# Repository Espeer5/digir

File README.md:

# DigiR Mobile Digital Mode Transceiver

The DigiR project is an effort to build a fully open source embedded mobile digital mode transciever design for ham operators. Many digital modes tend to require taking a computer running ham software into the field to make connections, which I consider to be a limitation in comparison to analog modes. This project is designed to remove that hurdle by creating a fully embedded platform that enables mobile digital operations.

The full tool chain of the proejct will be open source, avoiding any costly software licenses or other tools out of reach of the average radio hobbyist. An exception to the open-soruce nature of the project are the STM32Cube software packages used for configuring and flashing the STM32 MCU, but these are free packages that are accessible to the hobbyist.

Please note that this project has been significantly delayed due to hardware availability and lead times, which have changed the scope of the project. In particular, the ECP5 development board is very hard to come by at the moment, which is changing the scope of the project. Resulting from this issue some work must now be done to design a custom ECP5 hardware module for development, aside from the eventual custom radio board, increasing both the time and expense required.

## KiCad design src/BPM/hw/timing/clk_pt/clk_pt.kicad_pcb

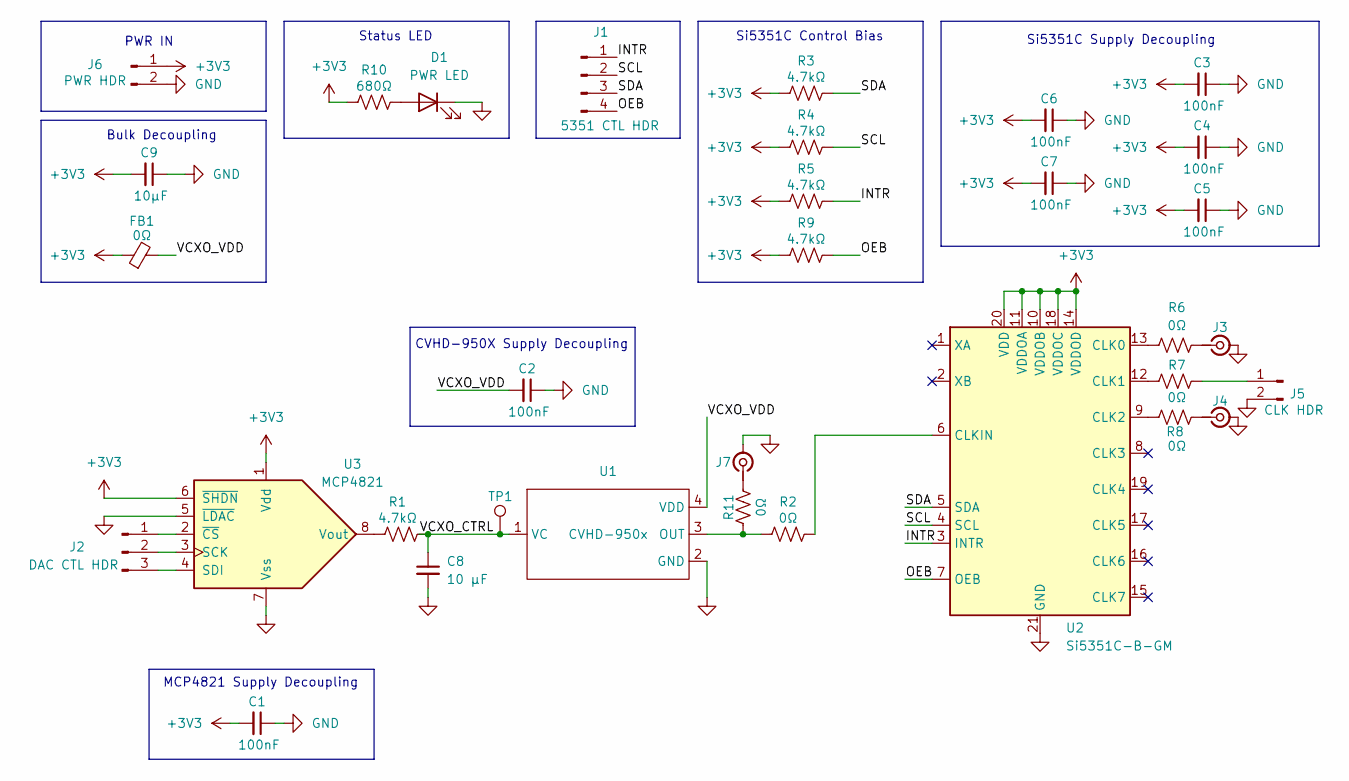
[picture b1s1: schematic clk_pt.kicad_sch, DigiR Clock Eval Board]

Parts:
C1, C2, C3, C4, C5, C6, C7: 100nF; C_0603_1608Metric
C8: 10 µF; C_0805_2012Metric
C9: 10µF; C_0805_2012Metric
D1: PWR LED; LED_0805_2012Metric
FB1: 0Ω; R_0603_1608Metric
J1: 5351 CTL HDR; PinHeader_1x04_P2.54mm_Vertical
J2: DAC CTL HDR; PinHeader_1x03_P2.54mm_Vertical
J3, J4, J7: SMA_Molex_73251-1153_EdgeMount_Horizontal
J5: CLK HDR; PinHeader_1x02_P2.54mm_Vertical
J6: PWR HDR; PinHeader_1x02_P2.54mm_Vertical
R1, R3, R4, R5, R9: 4.7kΩ; R_0603_1608Metric
R2, R6, R7, R8, R11: 0Ω; R_0603_1608Metric
R10: 680Ω; R_0603_1608Metric
TP1: TestPoint; TestPoint_THTPad_D2.0mm_Drill1.0mm
U1: CVHD-950x; OSC_CVHD-950X-100
U2: Si5351C-B-GM; QFN-20-1EP_4x4mm_P0.5mm_EP2.7x2.7mm
U3: MCP4821; SOIC-8_3.9x4.9mm_P1.27mm

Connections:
+3V3: C1.2, C3.2, C4.2, C5.2, C6.2, C7.2, C9.2, FB1.1, J6.1, R3.1, R4.1, R5.1, R9.1, R10.1, U2.10 (VDDOB), U2.11 (VDDOA), U2.14 (VDDOD), U2.18 (VDDOC), U2.20 (VDD), U3.1 (Vdd), U3.6 (~SHDN)
/INTR: J1.1, R5.2, U2.3 (INTR)
/OEB: J1.4, R9.2, U2.7 (OEB)
/SCL: J1.2, R4.2, U2.4 (SCL)
/SDA: J1.3, R3.2, U2.5 (SDA)
/VCXO_CTRL: C8.1, R1.2, TP1.1 (1_1), U1.1 (VC)
/VCXO_VDD: C2.2, FB1.2, U1.4 (VDD)
GND: C1.1, C2.1, C3.1, C4.1, C5.1, C6.1, C7.1, C8.2, C9.1, D1.1 (K), J3.2 (Ext), J4.2 (Ext), J5.2, J6.2, J7.2 (Ext), U1.2 (GND), U2.21 (GND), U3.5 (~LDAC), U3.7 (Vss)
unnamed: D1.2 (A), R10.2
unnamed: J2.1, U3.2 (~CS)
unnamed: J2.2, U3.3 (SCK)
unnamed: J2.3, U3.4 (SDI)
unnamed: J3.1 (In), R6.2
unnamed: J4.1 (In), R8.2
unnamed: J5.1, R7.2
unnamed: J7.1 (In), R11.2
unnamed: R2.1, R11.1, U1.3 (OUT)
unnamed: R6.1, U2.13 (CLK0)
unnamed: R7.1, U2.12 (CLK1)
unnamed: R8.1, U2.9 (CLK2)
unnamed: R2.2, U2.6 (CLKIN)
unnamed: R1.1, U3.8 (Vout)

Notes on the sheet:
CVHD-950X Supply Decoupling
Status LED
Si5351C Supply Decoupling
Bulk Decoupling
MCP4821 Supply Decoupling
Si5351C Control Bias
PWR IN

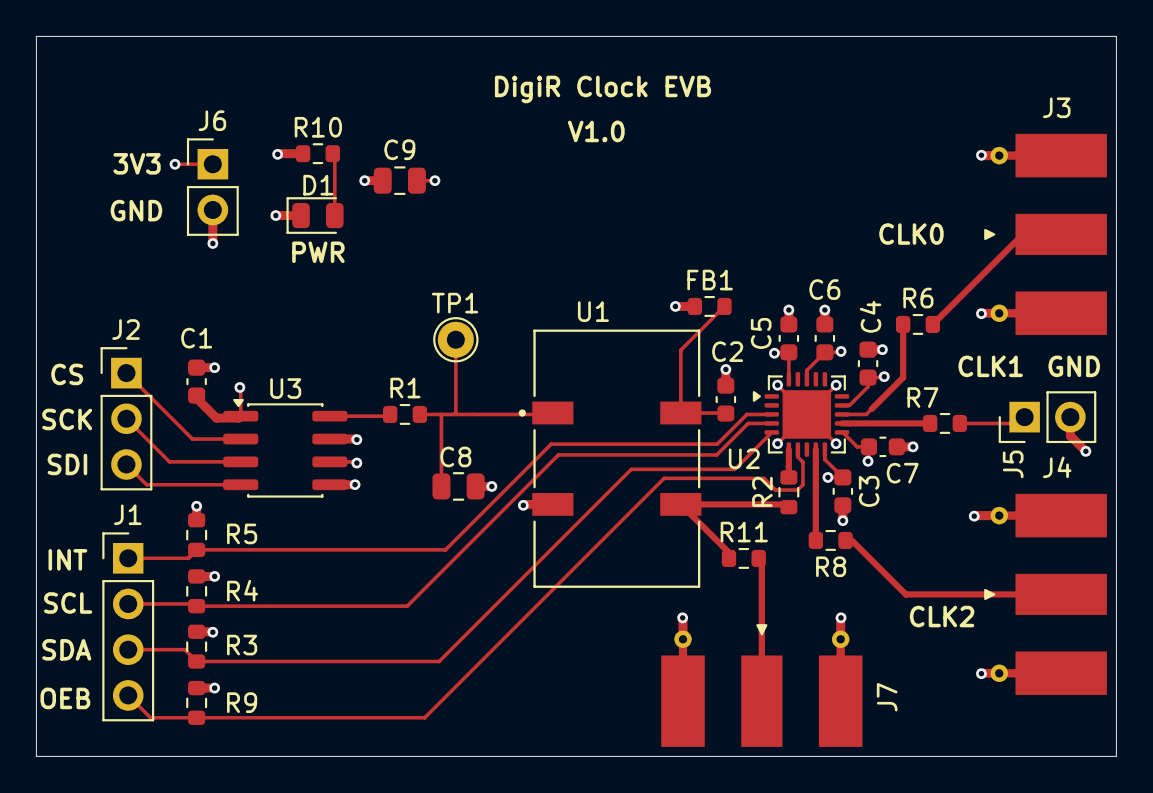
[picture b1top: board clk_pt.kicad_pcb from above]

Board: 4 copper layers, 60.0 x 40.0 mm, 33 parts (0 on the bottom side), 22 nets.
